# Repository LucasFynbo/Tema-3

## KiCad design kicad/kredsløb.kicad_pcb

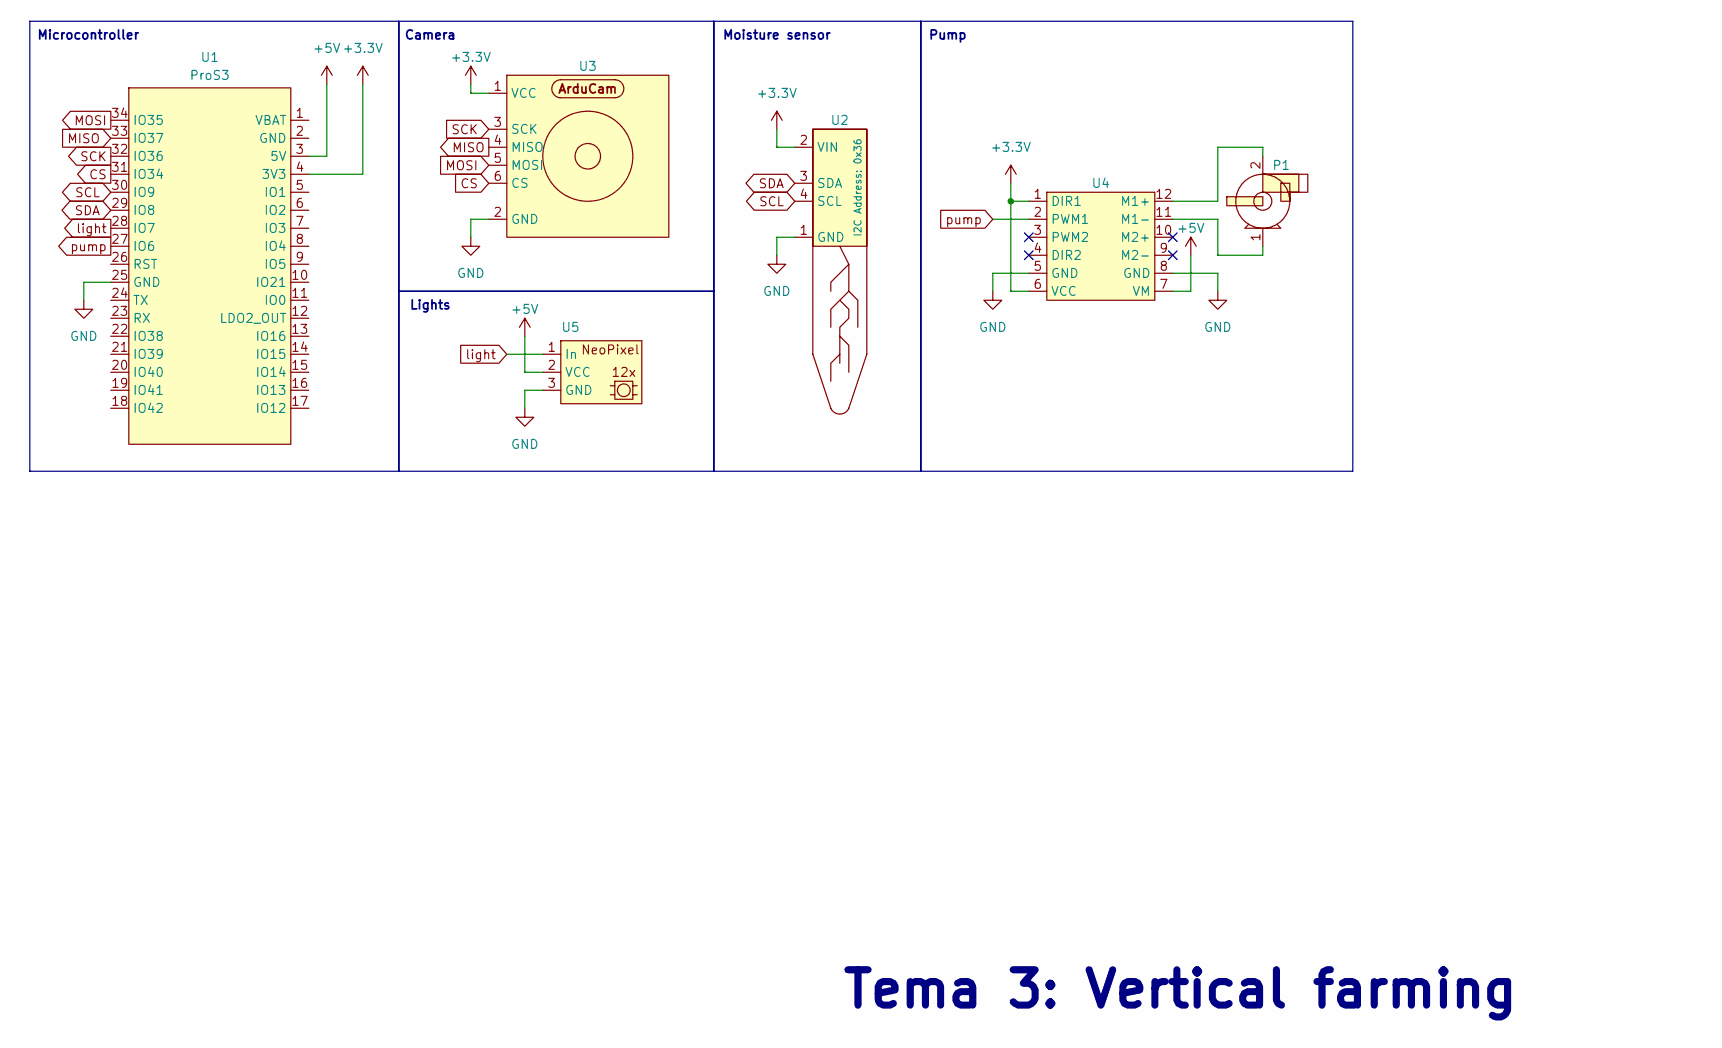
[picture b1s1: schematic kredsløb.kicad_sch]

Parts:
P1: PinHeader_1x02_P2.54mm_Vertical
U1: ProS3; ProS3_TH
U2: PinHeader_1x04_P2.54mm_Vertical
U3: 3MP; PinHeader_1x06_P2.54mm_Vertical
U4: TB6612FNG DfRobot motordriver module
U5: PinHeader_1x03_P2.54mm_Vertical

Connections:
+3.3V: U1.4 (3V3), U2.2 (VIN), U3.1 (VCC), U4.1 (DIR1), U4.6 (VCC)
+5V: U1.3 (5V), U4.7 (VM), U5.2 (VCC)
CS: U1.31 (IO34), U3.6 (CS)
GND: U1.25 (GND), U2.1 (GND), U3.2 (GND), U4.5 (GND), U4.8 (GND), U5.3 (GND)
MISO: U1.33 (IO37), U3.4 (MISO)
MOSI: U1.34 (IO35), U3.5 (MOSI)
unnamed: P1.2, U4.12 (M1+)
unnamed: P1.1, U4.11 (M1-)
SCK: U1.32 (IO36), U3.3 (SCK)
SCL: U1.30 (IO9), U2.4 (SCL)
SDA: U1.29 (IO8), U2.3 (SDA)
light: U1.28 (IO7), U5.1 (In)
pump: U1.27 (IO6), U4.2 (PWM1)

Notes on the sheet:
Lights
Camera
Microcontroller
Pump
Moisture sensor
Tema 3: Vertical farming

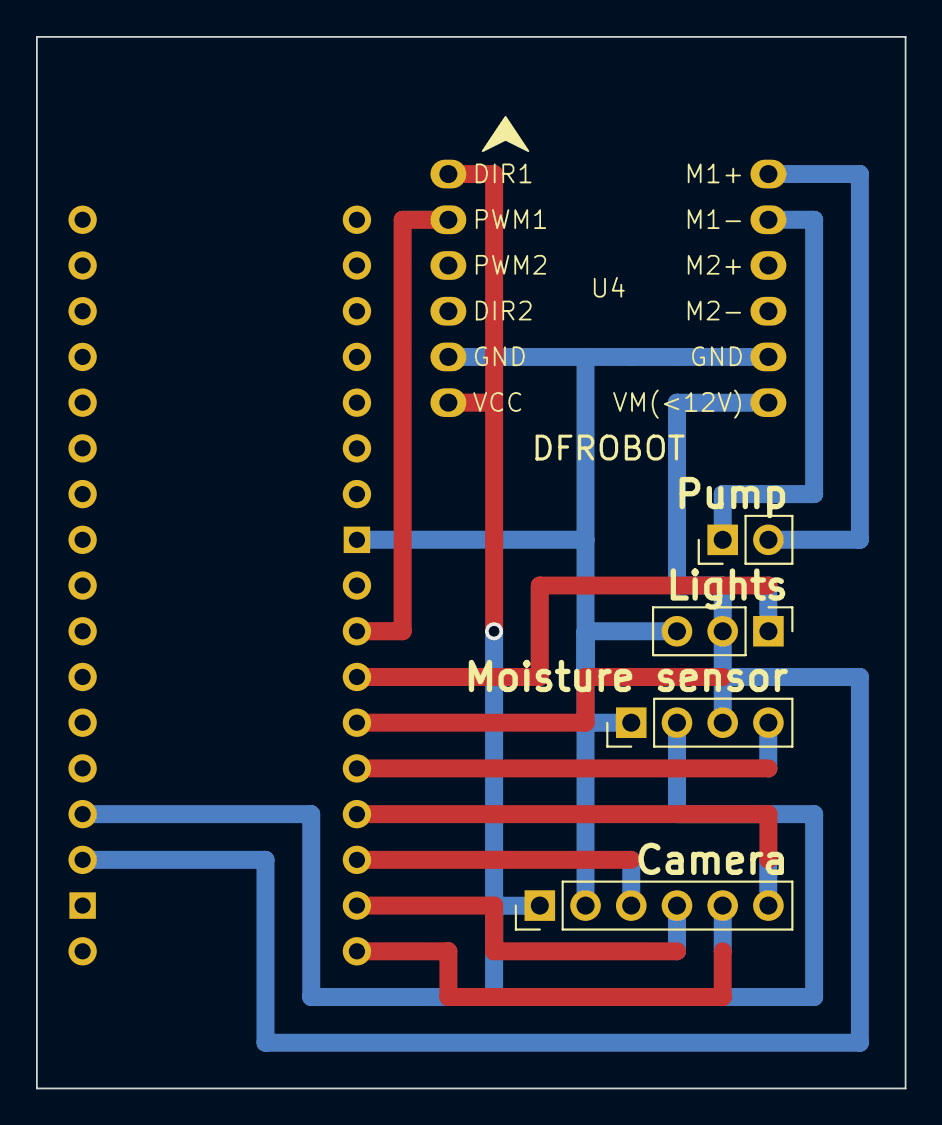
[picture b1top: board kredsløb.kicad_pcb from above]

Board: 4 copper layers, 48.3 x 58.4 mm, 6 parts (0 on the bottom side), 13 nets.

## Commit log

2024-02-23 Jpg send receive
    Foreløbig udgave
2024-02-23 arducam
    andreas udgave
2024-02-23 ringlight
    ringlight
2024-02-23 update ringlight
2024-02-24 initial struktur
2024-02-24 Rettelse
2024-02-24 Rettelse, billeder slettes ikke længere
2024-02-25 Opdatering med forsøg på interval
2024-02-26 davs
2024-02-26 add schedule for ringlight
2024-02-26 kicad
2024-02-26 Ændringer
2024-02-26 pump ready
2024-02-26 Update recvimages.py
    Tilføjer +1 til billede navn
2024-02-26 Create recvimages.py
    Tilføjer +1 til billede navn
2024-02-26 Update recvimages.py
    snake case op i den her
2024-02-26 recvimages til source
2024-02-26 vi håber det virker
2024-02-26 Return image_path
2024-02-26 Update- Wifi Script
2024-02-26 Creation of timelapse script
2024-03-05 Send og recieve images fra ESP32 til PC
2024-03-06 Blitz og fikset reinitialize for Camera() class hvert capture_images() funktions kald
2024-03-06 Send image incorporated
2024-03-06 slettet wifi
2024-03-06 06/03 update
2024-03-07 Recieve non-corrupted images of variable HTTP header lengths
2024-03-15 Final Commit
